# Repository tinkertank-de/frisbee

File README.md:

# Tinkertank's Frisbee - the sustainable Microcontroller

The Frisbee is your perfect tool to make new inventions out of e-waste, old toys and everyday objects.

The Frisbee is a microcontroller that can be plugged into any computer via USB and is recognized as a keyboard. Thus, similar to the Makey Makey ( https://makeymakey.com/ ), all conductive objects can be used to close circuits and trigger keystrokes. So a fork stuck in an apple becomes a space bar, or a high-five with your best friend becomes an arrow key.
If you still haven't had enough, you can turn the frisbee upside down to the dark side and dive deeper into the rabbit hole of makers and coders. On the backside and with the help of a block-based programming platform like OpenRoberta it is easy to run every actuator and sensor you find in the electronic waste to make your idea reality.

<br>*dark side of the ~~moon~~ frisbee*

# another microcontroller?

yes, why not.
it's plug and play like a [Makey Makey](https://makeymakey.com/), it's accessible with alligator clamps and easy to reprogram like the [Micro:bit](https://microbit.org//), it's cheap like an [Arduino Nano](https://store.arduino.cc/collections/most-popular/products/arduino-nano-every-with-headers) and it's capable of running micropython for super fast and compile-free programming.
Aaaaand it's got a super sweet RG-Bee-LED shining through the pcb for instant feedback. (reverse mounted neopixel LED)

# comparison sheet
|                            | Arduino Uno          | Makey Makey            | Micro:Bit            | Calliope          | Frisbee 2.0              |
| -------------------------- | -------------------- | ---------------------- | -------------------- | ----------------- | ------------------------ |
| Image                      |                      |                        |                      |                   |                          |
| forked from                |                      | Pro Micro /<br>Arduino Leonardo |             | Micro:Bit         | Raspberry Pi Pico        |
|                            |                      |                        |                      |                   |                          |
| hardware connectors        | jumper wires         | alligator clips   | alligator clips (limited) | alligator clips   | alligator clips          |
| cpu | ATmega328 (8-bit) | Atmel 32U4 | ARM Cortex-M0 (Nordic nRF51822) mit 32-Bit | ARM Cortex-M0 (Nordic nRF51822) mit 32-Bit | dual-core Arm Cortex-M0+ |
| native node based programming | NO                | NO                     | YES                  | YES               | YES                      |
| Bluetooth                  | NO                   | NO                     | YES                  | YES               | NO                       |
| Wifi                       | NO                   | NO                     | NO                   | NO                | NO                       |
| additional periphery       | LED                  | LED                    | Lagesensor, Buttons, LED Matrix, Kompass, RGB-LED, Temperatur, Lautsprecher, Mikrofon   | Lagesensor, Buttons, LED Matrix, Kompass, RGB-LED, Temperatur, Lautsprecher, Mikrofon | LED   |
| plug and play input device | NO                   | YES                    | NO                   | NO                | YES                      |
| made in                    | china                | china                  | ?                    | ?                 | D                        |
| hareware cost              | 23,50 €              | 55,00 €                | 29,00 €              | 40,00 €           | 15,00 €                  |

# fair trade & regional
We try to produce the frisbee boards as sustainable as possible and under fair working conditions in germany.
We are experimenting with different technologies like Paper-PCBs or printing with conductive paint on wood as an eco-friendly alternative to epoxy-based PCBs.

# open source
The Frisbee, like its core, the Pi Pico, is completely open source and can be further developed, modified and used by all users under the Creative Commons 4.0 license.

# about
Tinkertank is a stationary and mobile makerspace based in Ludwigsburg, Germany, empowering kids and adults to the creative use of technology.
www.tinkertank.de

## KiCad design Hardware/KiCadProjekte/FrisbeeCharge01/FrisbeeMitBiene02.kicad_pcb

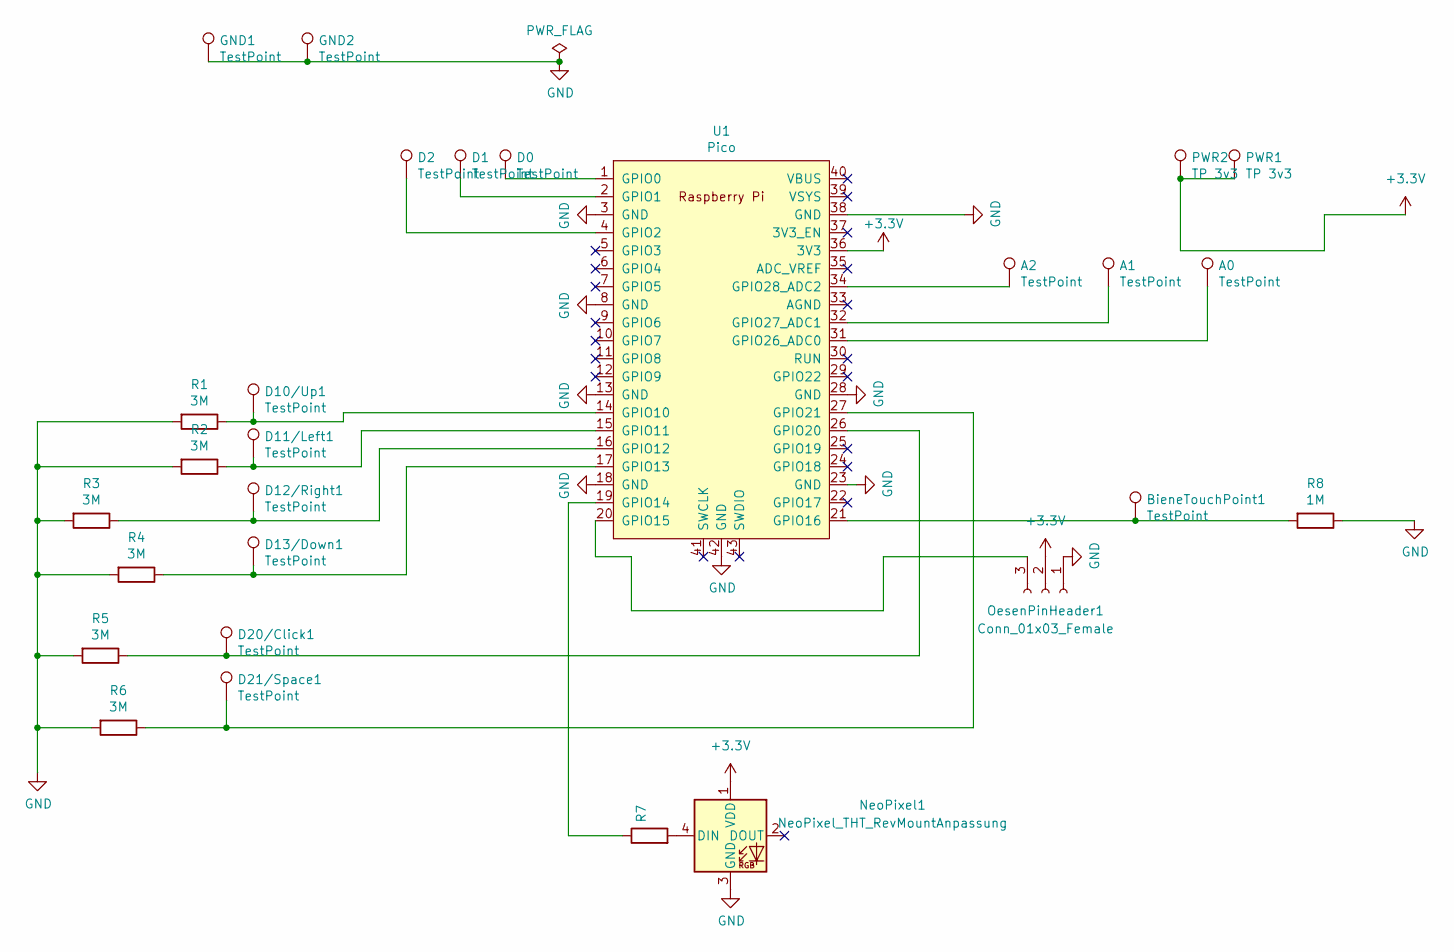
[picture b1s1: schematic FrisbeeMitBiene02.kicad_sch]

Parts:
A0, A1, A2: TestPoint; Edgeconnector_SMD_version
BieneTouchPoint1: TestPoint; testbiene
D0, D1, D2: TestPoint; Edgeconnector_SMD_version
D10/Up1, D11/Left1, D12/Right1, D13/Down1, D20/Click1, D21/Space1: TestPoint; KrokoConnector
GND1, GND2: TestPoint; Edgeconnector_SMD_version
NeoPixel1: NeoPixel_THT_RevMountAnpassung; NeoPixelReverseMountAnpassung
OesenPinHeader1: Conn_01x03_Female; PinHeader_1x03_P2.54mm_Vertical
PWR1, PWR2: TP 3v3; Edgeconnector_SMD_version
R1, R2, R3, R4, R5, R6: 3M
R7: (no value)
R8: 1M
U1: Pico; RPi_Pico_SMD_TH_meins

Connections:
+3V3: NeoPixel1.1 (VDD), OesenPinHeader1.2, PWR1.1, PWR2.1, U1.36 (3V3)
GND: GND1.1, GND2.1, NeoPixel1.3 (GND), OesenPinHeader1.1, R1.2, R2.2, R3.2, R4.2, R5.2, R6.2, R8.1, U1.3 (GND), U1.8 (GND), U1.13 (GND), U1.18 (GND), U1.23 (GND), U1.28 (GND), U1.38 (GND), U1.42 (GND)
unnamed: A0.1, U1.31 (GPIO26_ADC0)
unnamed: A1.1, U1.32 (GPIO27_ADC1)
unnamed: A2.1, U1.34 (GPIO28_ADC2)
unnamed: BieneTouchPoint1.1, R8.2, U1.21 (GPIO16)
unnamed: D0.1, U1.1 (GPIO0)
unnamed: D1.1, U1.2 (GPIO1)
unnamed: D2.1, U1.4 (GPIO2)
unnamed: D10/Up1.1, R1.1, U1.14 (GPIO10)
unnamed: D11/Left1.1, R2.1, U1.15 (GPIO11)
unnamed: D12/Right1.1, R3.1, U1.16 (GPIO12)
unnamed: D13/Down1.1, R4.1, U1.17 (GPIO13)
unnamed: D20/Click1.1, R5.1, U1.26 (GPIO20)
unnamed: D21/Space1.1, R6.1, U1.27 (GPIO21)
unnamed: NeoPixel1.4 (DIN), R7.2
unnamed: OesenPinHeader1.3, U1.20 (GPIO15)
unnamed: R7.1, U1.19 (GPIO14)

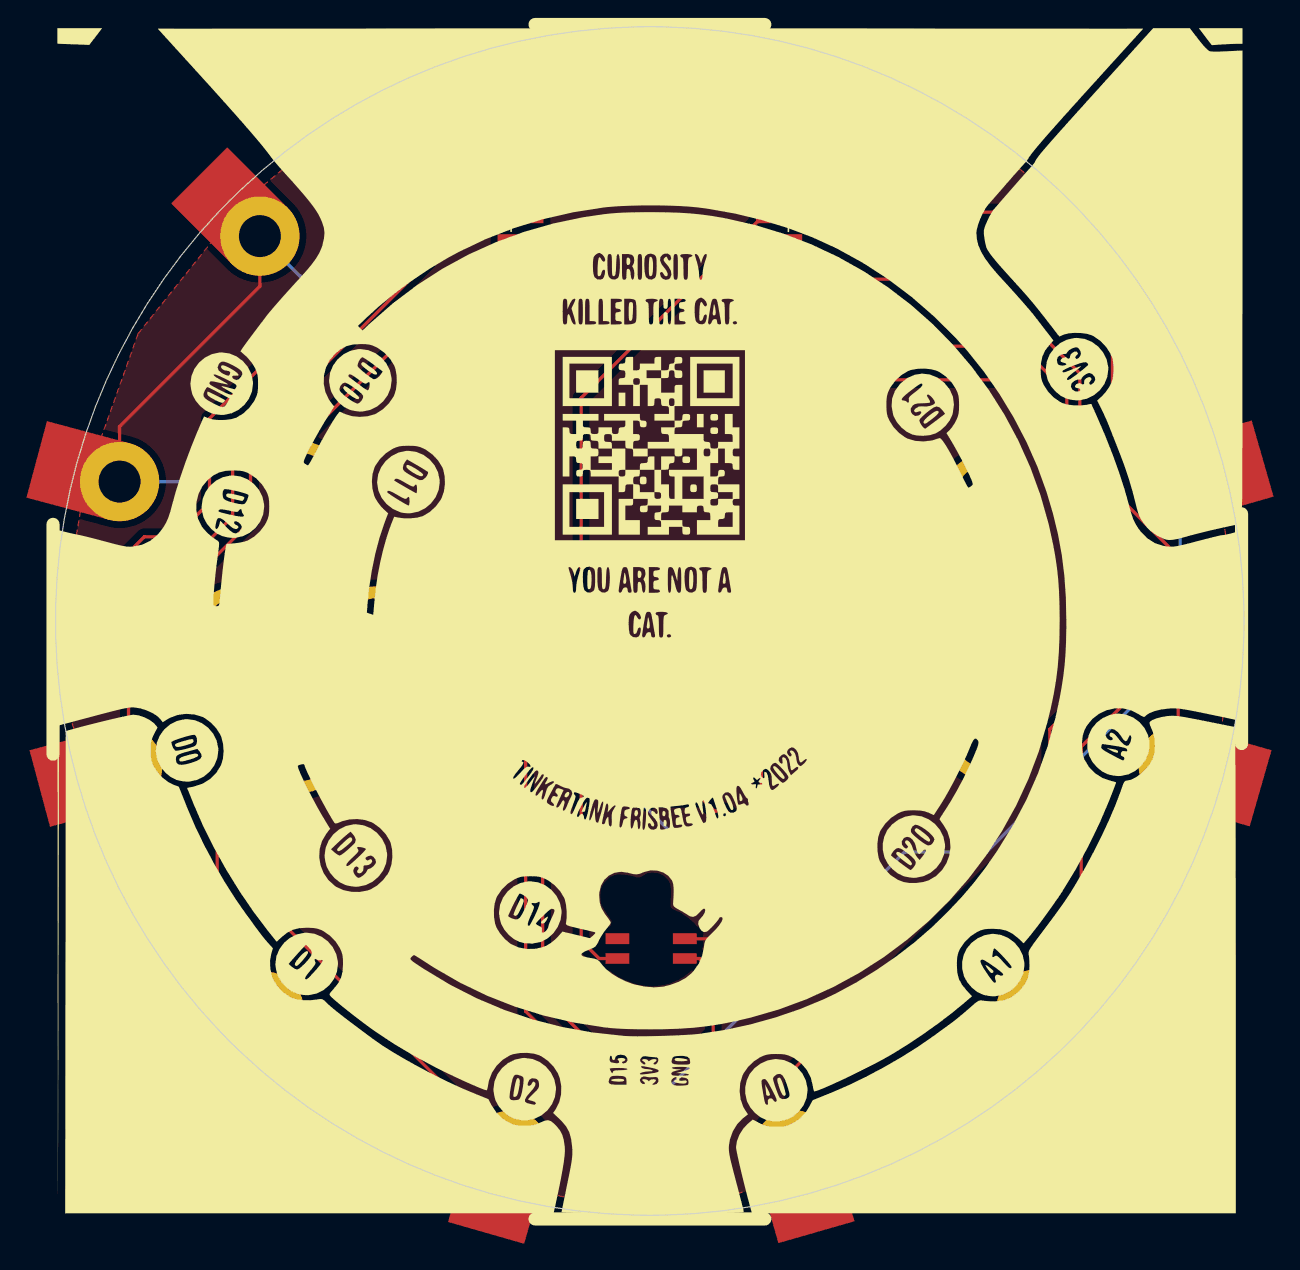
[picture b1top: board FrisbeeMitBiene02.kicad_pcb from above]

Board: 2 copper layers, 90.0 x 90.0 mm, 28 parts (1 on the bottom side), 18 nets.

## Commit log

2022-06-13 initial code
    Initial code for the frisbee made in Playpiper ( https://make.playpiper.com/ )
    based on circuitpython firmware
2022-06-13 intitial code
    Initial code for the frisbee made in Playpiper ( https://make.playpiper.com/ )
    based on circuitpython firmware
2022-06-13 v001
2022-07-01 zweites update heute
2022-07-01 CodeBasis_Frisbee_01
    upload von SchlöÖö
2022-07-01 prints rausgenommen
2022-07-02 Update CodeBase01_mitNeopixel.py
    test test test
2022-07-04 derbe aufgeräumt.
    ein funktion für pin lesen, eine funktion für pins auswerten und tasten aktivieren
    statt ja eine funktion pro taste
2022-07-05 code.py is the new standard code
    with neopixel bee
2022-07-12 KicadProject Stand Charge01
2022-07-13 new file structure
2022-07-14 motorbee mit rädern
